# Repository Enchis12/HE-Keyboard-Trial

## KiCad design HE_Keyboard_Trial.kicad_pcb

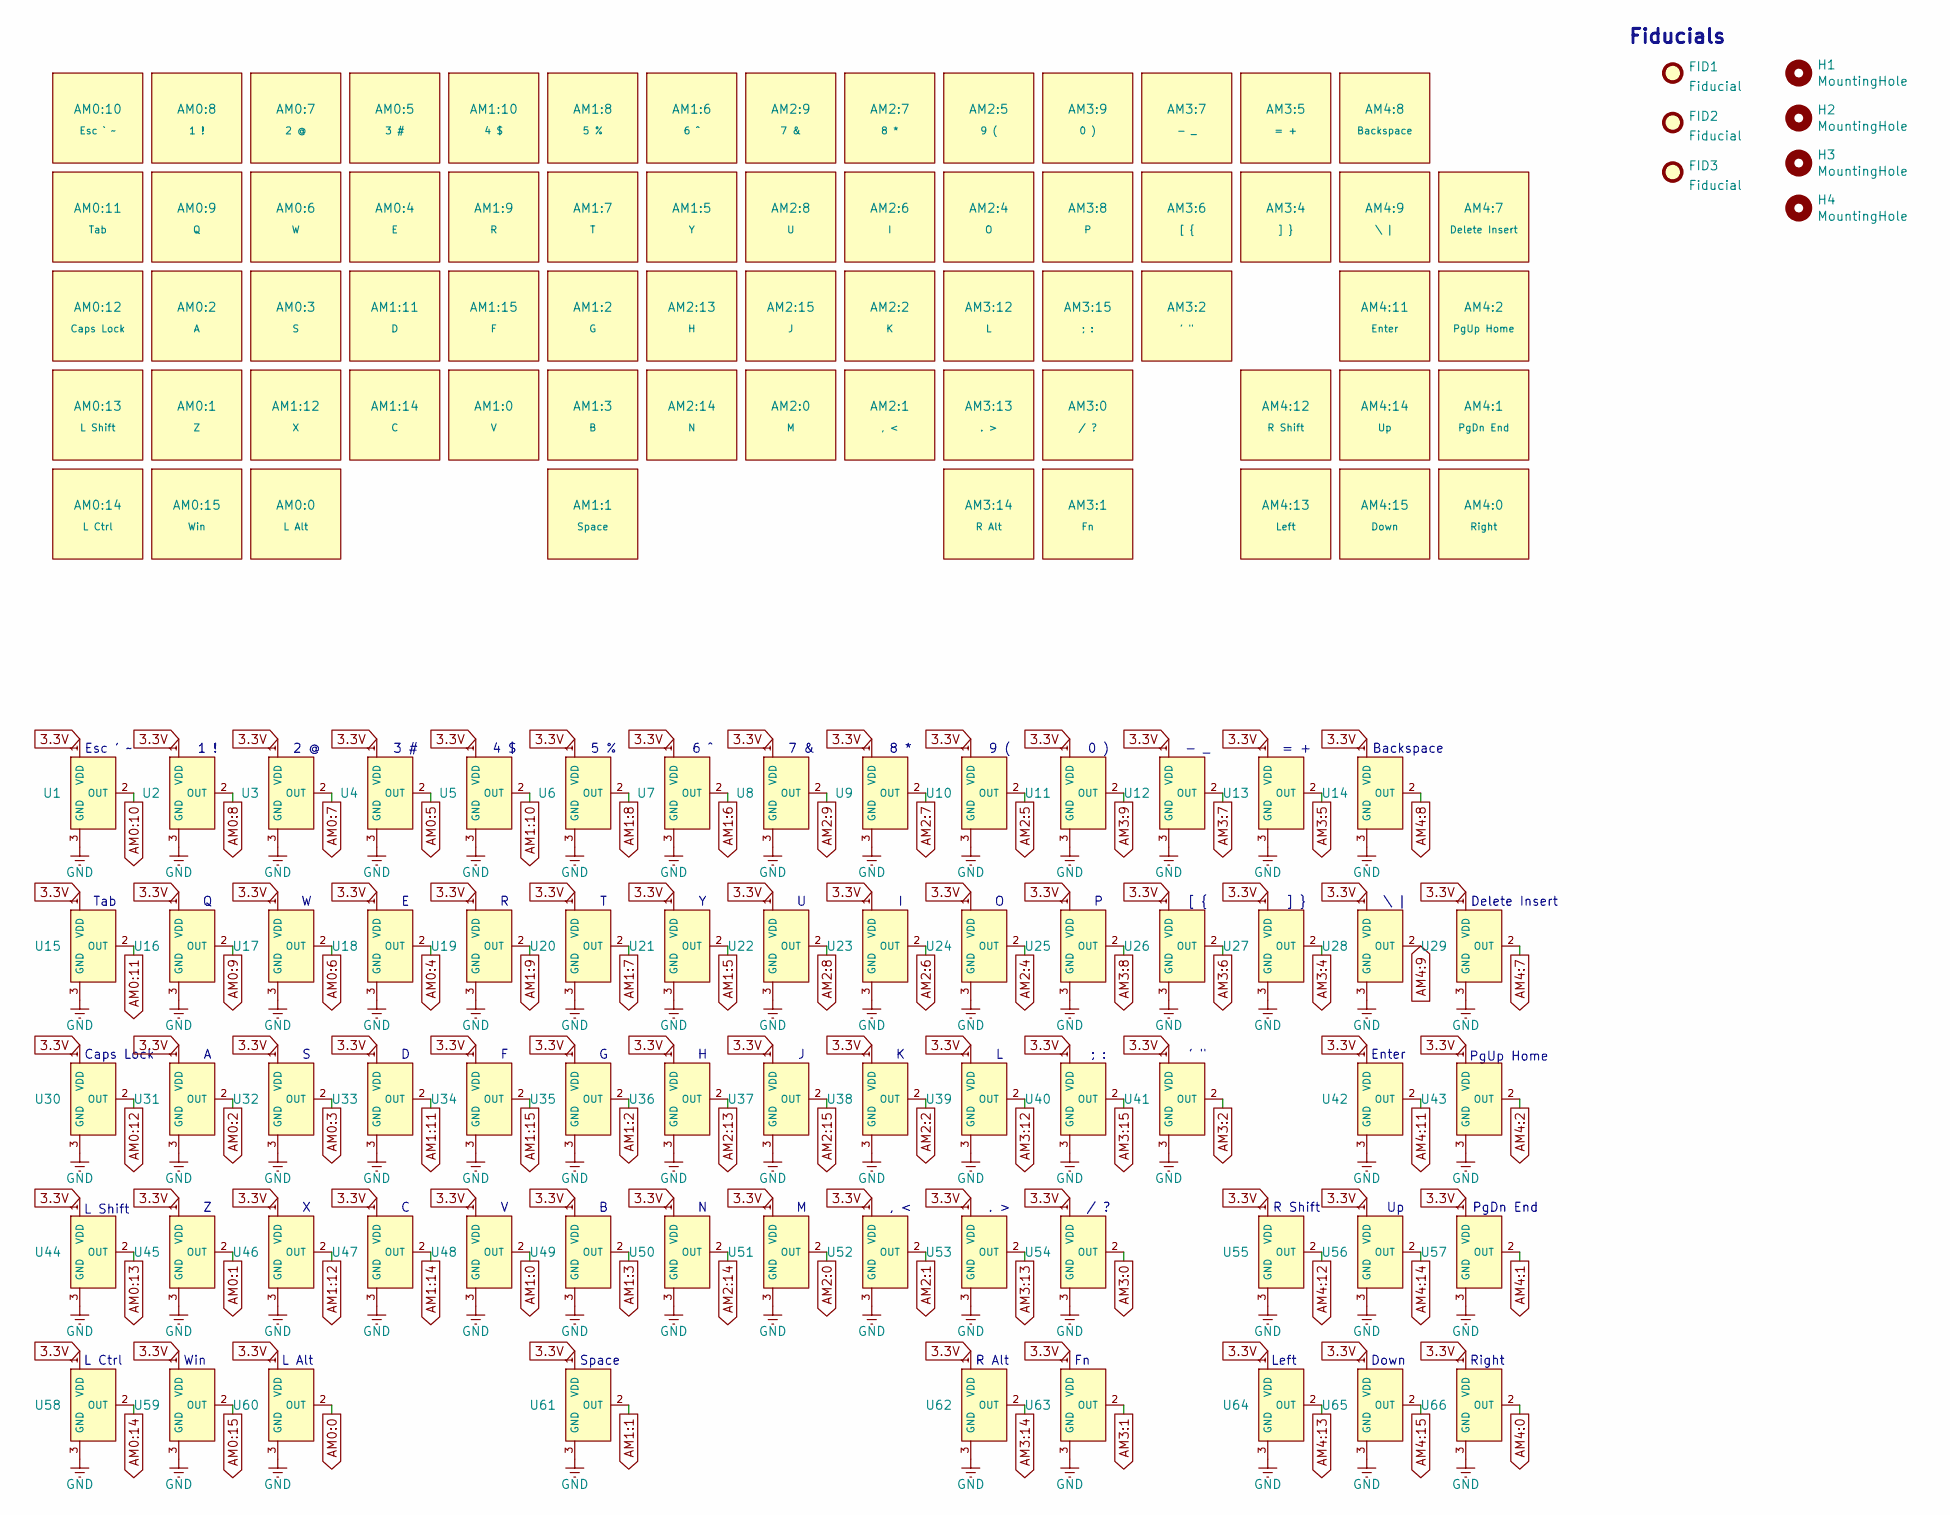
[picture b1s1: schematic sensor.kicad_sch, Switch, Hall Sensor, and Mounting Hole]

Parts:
AM0:0: L Alt; MX_Gateron_HE_1.25u
AM0:1: Z; MX_Gateron_HE_1u
AM0:2: A; MX_Gateron_HE_1u
AM0:3: S; MX_Gateron_HE_1u
AM0:4: E; MX_Gateron_HE_1u
AM0:5: 3 #; MX_Gateron_HE_1u
AM0:6: W; MX_Gateron_HE_1u
AM0:7: 2 @; MX_Gateron_HE_1u
AM0:8: 1 !; MX_Gateron_HE_1u
AM0:9: Q; MX_Gateron_HE_1u
AM0:10: Esc ` ~; MX_Gateron_HE_1u
AM0:11: Tab; MX_Gateron_HE_1.5u
AM0:12: Caps Lock; MX_Gateron_HE_1.75u
AM0:13: L Shift; MX_Gateron_HE_2.25u_Stab
AM0:14: L Ctrl; MX_Gateron_HE_1.25u
AM0:15: Win; MX_Gateron_HE_1.25u
AM1:0: V; MX_Gateron_HE_1u
AM1:1: Space; MX_Gateron_HE_6.25u_Stab
AM1:2: G; MX_Gateron_HE_1u
AM1:3: B; MX_Gateron_HE_1u
AM1:5: Y; MX_Gateron_HE_1u
AM1:6: 6 ^; MX_Gateron_HE_1u
AM1:7: T; MX_Gateron_HE_1u
AM1:8: 5 %; MX_Gateron_HE_1u
AM1:9: R; MX_Gateron_HE_1u
AM1:10: 4 $; MX_Gateron_HE_1u
AM1:11: D; MX_Gateron_HE_1u
AM1:12: X; MX_Gateron_HE_1u
AM1:14: C; MX_Gateron_HE_1u
AM1:15: F; MX_Gateron_HE_1u
AM2:0: M; MX_Gateron_HE_1u
AM2:1: , <; MX_Gateron_HE_1u
AM2:2: K; MX_Gateron_HE_1u
AM2:4: O; MX_Gateron_HE_1u
AM2:5: 9 (; MX_Gateron_HE_1u
AM2:6: I; MX_Gateron_HE_1u
AM2:7: 8 *; MX_Gateron_HE_1u
AM2:8: U; MX_Gateron_HE_1u
AM2:9: 7 &; MX_Gateron_HE_1u
AM2:13: H; MX_Gateron_HE_1u
AM2:14: N; MX_Gateron_HE_1u
AM2:15: J; MX_Gateron_HE_1u
AM3:0: / ?; MX_Gateron_HE_1u
AM3:1: Fn; MX_Gateron_HE_1.25u
AM3:2: ' "; MX_Gateron_HE_1u
AM3:4: ] }; MX_Gateron_HE_1u
AM3:5: = +; MX_Gateron_HE_1u
AM3:6: [ {; MX_Gateron_HE_1u
AM3:7: - _; MX_Gateron_HE_1u
AM3:8: P; MX_Gateron_HE_1u
AM3:9: 0 ); MX_Gateron_HE_1u
AM3:12: L; MX_Gateron_HE_1u
AM3:13: . >; MX_Gateron_HE_1u
AM3:14: R Alt; MX_Gateron_HE_1.25u
AM3:15: ; :; MX_Gateron_HE_1u
AM4:0: Right; MX_Gateron_HE_1u
AM4:1: PgDn End; MX_Gateron_HE_1u
AM4:2: PgUp Home; MX_Gateron_HE_1u
AM4:7: Delete Insert; MX_Gateron_HE_1u
AM4:8: Backspace; MX_Gateron_HE_2u_Stab
AM4:9: \ |; MX_Gateron_HE_1.5u
AM4:11: Enter; MX_Gateron_HE_2.25u_Stab
AM4:12: R Shift; MX_Gateron_HE_1.75u
AM4:13: Left; MX_Gateron_HE_1u
AM4:14: Up; MX_Gateron_HE_1u
AM4:15: Down; MX_Gateron_HE_1u
FID1, FID2, FID3: Fiducial; Fiducial_1mm_Mask2mm
H1, H2, H3, H4: MountingHole; MountingHole_2.2mm_M2
U1, U2, U3, U4, U5, U6, U7, U8, U9, U10, U11, U12, U13, U14, U15, U16, U17, U18, U19, U20, U21, U22, U23, U24, U25, U26, U27, U28, U29, U30, U31, U32, U33, U34, U35, U36, U37, U38, U39, U40, U41, U42, U43, U44, U45, U46, U47, U48, U49, U50, U51, U52, U53, U54, U55, U56, U57, U58, U59, U60, U61, U62, U63, U64, U65, U66: Hall_Sensor; GH39FKSW_OH49E-S; MPN GH39FKSW; LCSC Part C266230

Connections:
3.3V: U1.1 (VDD), U2.1 (VDD), U3.1 (VDD), U4.1 (VDD), U5.1 (VDD), U6.1 (VDD), U7.1 (VDD), U8.1 (VDD), U9.1 (VDD), U10.1 (VDD), U11.1 (VDD), U12.1 (VDD), U13.1 (VDD), U14.1 (VDD), U15.1 (VDD), U16.1 (VDD), U17.1 (VDD), U18.1 (VDD), U19.1 (VDD), U20.1 (VDD), U21.1 (VDD), U22.1 (VDD), U23.1 (VDD), U24.1 (VDD), U25.1 (VDD), U26.1 (VDD), U27.1 (VDD), U28.1 (VDD), U29.1 (VDD), U30.1 (VDD), U31.1 (VDD), U32.1 (VDD), U33.1 (VDD), U34.1 (VDD), U35.1 (VDD), U36.1 (VDD), U37.1 (VDD), U38.1 (VDD), U39.1 (VDD), U40.1 (VDD), U41.1 (VDD), U42.1 (VDD), U43.1 (VDD), U44.1 (VDD), U45.1 (VDD), U46.1 (VDD), U47.1 (VDD), U48.1 (VDD), U49.1 (VDD), U50.1 (VDD), U51.1 (VDD), U52.1 (VDD), U53.1 (VDD), U54.1 (VDD), U55.1 (VDD), U56.1 (VDD), U57.1 (VDD), U58.1 (VDD), U59.1 (VDD), U60.1 (VDD), U61.1 (VDD), U62.1 (VDD), U63.1 (VDD), U64.1 (VDD), U65.1 (VDD), U66.1 (VDD); also elsewhere on the board
AM0:0: U60.2 (OUT); also elsewhere on the board
AM0:1: U45.2 (OUT); also elsewhere on the board
AM0:2: U31.2 (OUT); also elsewhere on the board
AM0:3: U32.2 (OUT); also elsewhere on the board
AM0:4: U18.2 (OUT); also elsewhere on the board
AM0:5: U4.2 (OUT); also elsewhere on the board
AM0:6: U17.2 (OUT); also elsewhere on the board
AM0:7: U3.2 (OUT); also elsewhere on the board
AM0:8: U2.2 (OUT); also elsewhere on the board
AM0:9: U16.2 (OUT); also elsewhere on the board
AM0:10: U1.2 (OUT); also elsewhere on the board
AM0:11: U15.2 (OUT); also elsewhere on the board
AM0:12: U30.2 (OUT); also elsewhere on the board
AM0:13: U44.2 (OUT); also elsewhere on the board
AM0:14: U58.2 (OUT); also elsewhere on the board
AM0:15: U59.2 (OUT); also elsewhere on the board
AM1:0: U48.2 (OUT); also elsewhere on the board
AM1:1: U61.2 (OUT); also elsewhere on the board
AM1:2: U35.2 (OUT); also elsewhere on the board
AM1:3: U49.2 (OUT); also elsewhere on the board
AM1:5: U21.2 (OUT); also elsewhere on the board
AM1:6: U7.2 (OUT); also elsewhere on the board
AM1:7: U20.2 (OUT); also elsewhere on the board
AM1:8: U6.2 (OUT); also elsewhere on the board
AM1:9: U19.2 (OUT); also elsewhere on the board
AM1:10: U5.2 (OUT); also elsewhere on the board
AM1:11: U33.2 (OUT); also elsewhere on the board
AM1:12: U46.2 (OUT); also elsewhere on the board
AM1:14: U47.2 (OUT); also elsewhere on the board
AM1:15: U34.2 (OUT); also elsewhere on the board
AM2:0: U51.2 (OUT); also elsewhere on the board
AM2:1: U52.2 (OUT); also elsewhere on the board
AM2:2: U38.2 (OUT); also elsewhere on the board
AM2:4: U24.2 (OUT); also elsewhere on the board
AM2:5: U10.2 (OUT); also elsewhere on the board
AM2:6: U23.2 (OUT); also elsewhere on the board
AM2:7: U9.2 (OUT); also elsewhere on the board
AM2:8: U22.2 (OUT); also elsewhere on the board
AM2:9: U8.2 (OUT); also elsewhere on the board
AM2:13: U36.2 (OUT); also elsewhere on the board
AM2:14: U50.2 (OUT); also elsewhere on the board
AM2:15: U37.2 (OUT); also elsewhere on the board
AM3:0: U54.2 (OUT); also elsewhere on the board
AM3:1: U63.2 (OUT); also elsewhere on the board
AM3:2: U41.2 (OUT); also elsewhere on the board
AM3:4: U27.2 (OUT); also elsewhere on the board
AM3:5: U13.2 (OUT); also elsewhere on the board
AM3:6: U26.2 (OUT); also elsewhere on the board
AM3:7: U12.2 (OUT); also elsewhere on the board
AM3:8: U25.2 (OUT); also elsewhere on the board
AM3:9: U11.2 (OUT); also elsewhere on the board
AM3:12: U39.2 (OUT); also elsewhere on the board
AM3:13: U53.2 (OUT); also elsewhere on the board
AM3:14: U62.2 (OUT); also elsewhere on the board
AM3:15: U40.2 (OUT); also elsewhere on the board
AM4:0: U66.2 (OUT); also elsewhere on the board
AM4:1: U57.2 (OUT); also elsewhere on the board
AM4:2: U43.2 (OUT); also elsewhere on the board
AM4:7: U29.2 (OUT); also elsewhere on the board
AM4:8: U14.2 (OUT); also elsewhere on the board
AM4:9: U28.2 (OUT); also elsewhere on the board
AM4:11: U42.2 (OUT); also elsewhere on the board
AM4:12: U55.2 (OUT); also elsewhere on the board
AM4:13: U64.2 (OUT); also elsewhere on the board
AM4:14: U56.2 (OUT); also elsewhere on the board
AM4:15: U65.2 (OUT); also elsewhere on the board
GND: U1.3 (GND), U2.3 (GND), U3.3 (GND), U4.3 (GND), U5.3 (GND), U6.3 (GND), U7.3 (GND), U8.3 (GND), U9.3 (GND), U10.3 (GND), U11.3 (GND), U12.3 (GND), U13.3 (GND), U14.3 (GND), U15.3 (GND), U16.3 (GND), U17.3 (GND), U18.3 (GND), U19.3 (GND), U20.3 (GND), U21.3 (GND), U22.3 (GND), U23.3 (GND), U24.3 (GND), U25.3 (GND), U26.3 (GND), U27.3 (GND), U28.3 (GND), U29.3 (GND), U30.3 (GND), U31.3 (GND), U32.3 (GND), U33.3 (GND), U34.3 (GND), U35.3 (GND), U36.3 (GND), U37.3 (GND), U38.3 (GND), U39.3 (GND), U40.3 (GND), U41.3 (GND), U42.3 (GND), U43.3 (GND), U44.3 (GND), U45.3 (GND), U46.3 (GND), U47.3 (GND), U48.3 (GND), U49.3 (GND), U50.3 (GND), U51.3 (GND), U52.3 (GND), U53.3 (GND), U54.3 (GND), U55.3 (GND), U56.3 (GND), U57.3 (GND), U58.3 (GND), U59.3 (GND), U60.3 (GND), U61.3 (GND), U62.3 (GND), U63.3 (GND), U64.3 (GND), U65.3 (GND), U66.3 (GND); also elsewhere on the board

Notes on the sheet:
Fiducials
Delete Insert
PgUp Home
] }
Space
. >
Backspace
PgDn End
, <
Win
Left
5 %
Enter
\ |
4 $
Down
3 #
Right
R Shift
= +
Tab
7 &
Caps Lock
2 @
L Alt
Esc ' ~
R Alt
; :
0 )
- _
9 (
1 !
/ ?
[ {
' "
6 ^
L Ctrl
8 *
L Shift
